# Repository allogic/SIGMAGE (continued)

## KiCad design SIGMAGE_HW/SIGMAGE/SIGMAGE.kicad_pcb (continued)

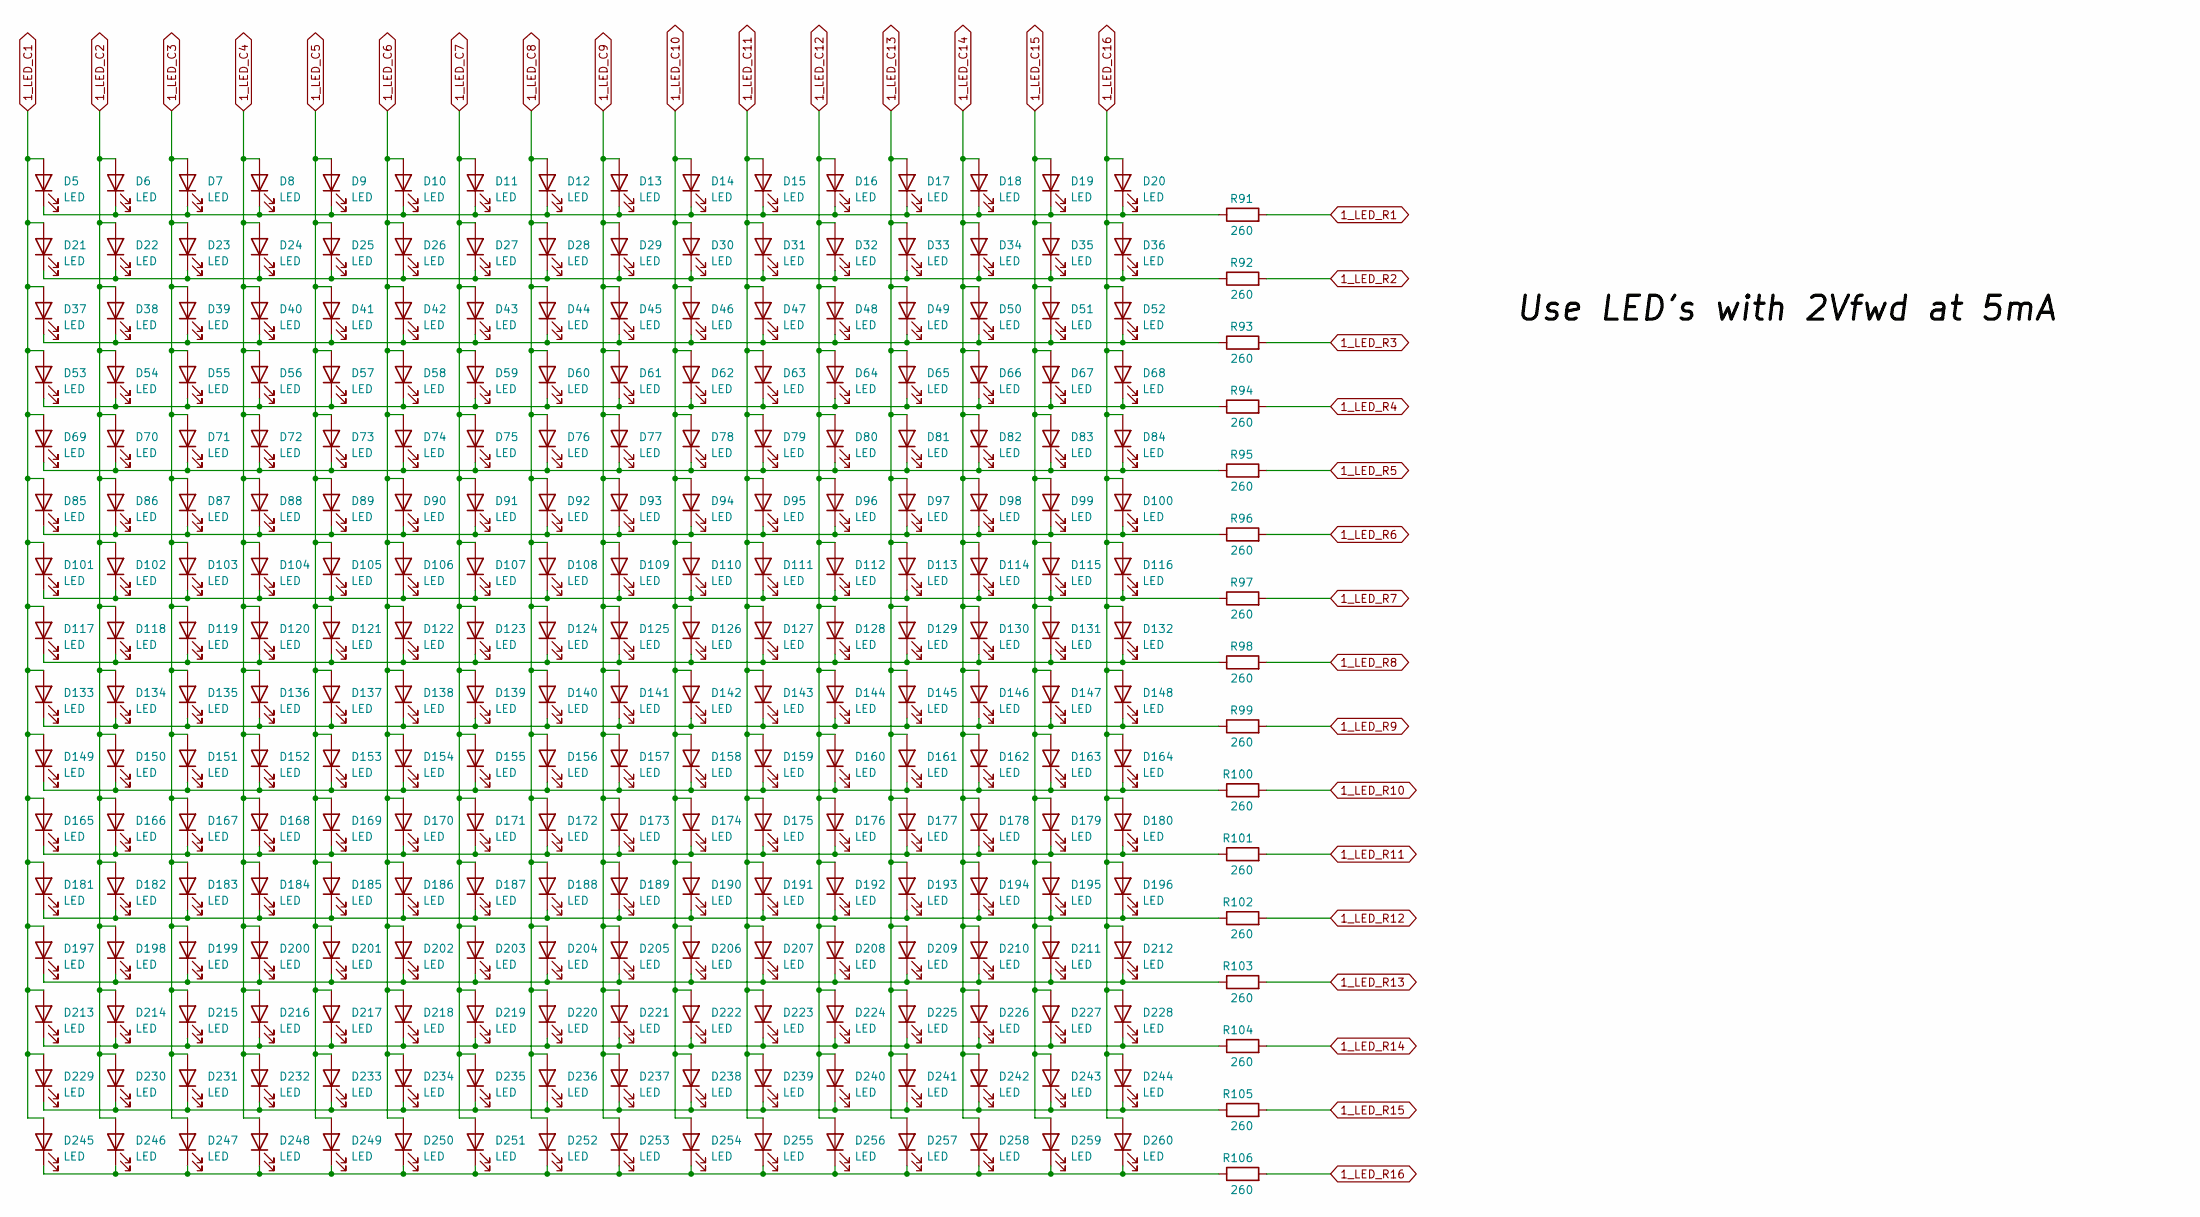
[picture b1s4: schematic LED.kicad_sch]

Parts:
D5, D6, D7, D8, D9, D10, D11, D12, D13, D14, D15, D16, D17, D18, D19, D20, D21, D22, D23, D24, D25, D26, D27, D28, D29, D30, D31, D32, D33, D34, D35, D36, D37, D38, D39, D40, D41, D42, D43, D44, D45, D46, D47, D48, D49, D50, D51, D52, D53, D54, D55, D56, D57, D58, D59, D60, D61, D62, D63, D64, D65, D66, D67, D68, D69, D70, D71, D72, D73, D74, D75, D76, D77, D78, D79, D80, D81, D82, D83, D84, D85, D86, D87, D88, D89, D90, D91, D92, D93, D94, D95, D96, D97, D98, D99, D100, D101, D102, D103, D104, D105, D106, D107, D108, D109, D110, D111, D112, D113, D114, D115, D116, D117, D118, D119, D120, D121, D122, D123, D124, D125, D126, D127, D128, D129, D130, D131, D132, D133, D134, D135, D136, D137, D138, D139, D140, D141, D142, D143, D144, D145, D146, D147, D148, D149, D150, D151, D152, D153, D154, D155, D156, D157, D158, D159, D160, D161, D162, D163, D164, D165, D166, D167, D168, D169, D170, D171, D172, D173, D174, D175, D176, D177, D178, D179, D180, D181, D182, D183, D184, D185, D186, D187, D188, D189, D190, D191, D192, D193, D194, D195, D196, D197, D198, D199, D200, D201, D202, D203, D204, D205, D206, D207, D208, D209, D210, D211, D212, D213, D214, D215, D216, D217, D218, D219, D220, D221, D222, D223, D224, D225, D226, D227, D228, D229, D230, D231, D232, D233, D234, D235, D236, D237, D238, D239, D240, D241, D242, D243, D244, D245, D246, D247, D248, D249, D250, D251, D252, D253, D254, D255, D256, D257, D258, D259, D260: LED; LED_0603_1608Metric
R91, R92, R93, R94, R95, R96, R97, R98, R99, R100, R101, R102, R103, R104, R105, R106: 260; R_0603_1608Metric

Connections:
1_LED_C1: D5.2 (A), D21.2 (A), D37.2 (A), D53.2 (A), D69.2 (A), D85.2 (A), D101.2 (A), D117.2 (A), D133.2 (A), D149.2 (A), D165.2 (A), D181.2 (A), D197.2 (A), D213.2 (A), D229.2 (A), D245.2 (A); also elsewhere on the board
1_LED_C2: D6.2 (A), D22.2 (A), D38.2 (A), D54.2 (A), D70.2 (A), D86.2 (A), D102.2 (A), D118.2 (A), D134.2 (A), D150.2 (A), D166.2 (A), D182.2 (A), D198.2 (A), D214.2 (A), D230.2 (A), D246.2 (A); also elsewhere on the board
1_LED_C3: D7.2 (A), D23.2 (A), D39.2 (A), D55.2 (A), D71.2 (A), D87.2 (A), D103.2 (A), D119.2 (A), D135.2 (A), D151.2 (A), D167.2 (A), D183.2 (A), D199.2 (A), D215.2 (A), D231.2 (A), D247.2 (A); also elsewhere on the board
1_LED_C4: D8.2 (A), D24.2 (A), D40.2 (A), D56.2 (A), D72.2 (A), D88.2 (A), D104.2 (A), D120.2 (A), D136.2 (A), D152.2 (A), D168.2 (A), D184.2 (A), D200.2 (A), D216.2 (A), D232.2 (A), D248.2 (A); also elsewhere on the board
1_LED_C5: D9.2 (A), D25.2 (A), D41.2 (A), D57.2 (A), D73.2 (A), D89.2 (A), D105.2 (A), D121.2 (A), D137.2 (A), D153.2 (A), D169.2 (A), D185.2 (A), D201.2 (A), D217.2 (A), D233.2 (A), D249.2 (A); also elsewhere on the board
1_LED_C6: D10.2 (A), D26.2 (A), D42.2 (A), D58.2 (A), D74.2 (A), D90.2 (A), D106.2 (A), D122.2 (A), D138.2 (A), D154.2 (A), D170.2 (A), D186.2 (A), D202.2 (A), D218.2 (A), D234.2 (A), D250.2 (A); also elsewhere on the board
1_LED_C7: D11.2 (A), D27.2 (A), D43.2 (A), D59.2 (A), D75.2 (A), D91.2 (A), D107.2 (A), D123.2 (A), D139.2 (A), D155.2 (A), D171.2 (A), D187.2 (A), D203.2 (A), D219.2 (A), D235.2 (A), D251.2 (A); also elsewhere on the board
1_LED_C8: D12.2 (A), D28.2 (A), D44.2 (A), D60.2 (A), D76.2 (A), D92.2 (A), D108.2 (A), D124.2 (A), D140.2 (A), D156.2 (A), D172.2 (A), D188.2 (A), D204.2 (A), D220.2 (A), D236.2 (A), D252.2 (A); also elsewhere on the board
1_LED_C9: D13.2 (A), D29.2 (A), D45.2 (A), D61.2 (A), D77.2 (A), D93.2 (A), D109.2 (A), D125.2 (A), D141.2 (A), D157.2 (A), D173.2 (A), D189.2 (A), D205.2 (A), D221.2 (A), D237.2 (A), D253.2 (A); also elsewhere on the board
1_LED_C10: D14.2 (A), D30.2 (A), D46.2 (A), D62.2 (A), D78.2 (A), D94.2 (A), D110.2 (A), D126.2 (A), D142.2 (A), D158.2 (A), D174.2 (A), D190.2 (A), D206.2 (A), D222.2 (A), D238.2 (A), D254.2 (A); also elsewhere on the board
1_LED_C11: D15.2 (A), D31.2 (A), D47.2 (A), D63.2 (A), D79.2 (A), D95.2 (A), D111.2 (A), D127.2 (A), D143.2 (A), D159.2 (A), D175.2 (A), D191.2 (A), D207.2 (A), D223.2 (A), D239.2 (A), D255.2 (A); also elsewhere on the board
1_LED_C12: D16.2 (A), D32.2 (A), D48.2 (A), D64.2 (A), D80.2 (A), D96.2 (A), D112.2 (A), D128.2 (A), D144.2 (A), D160.2 (A), D176.2 (A), D192.2 (A), D208.2 (A), D224.2 (A), D240.2 (A), D256.2 (A); also elsewhere on the board
1_LED_C13: D17.2 (A), D33.2 (A), D49.2 (A), D65.2 (A), D81.2 (A), D97.2 (A), D113.2 (A), D129.2 (A), D145.2 (A), D161.2 (A), D177.2 (A), D193.2 (A), D209.2 (A), D225.2 (A), D241.2 (A), D257.2 (A); also elsewhere on the board
1_LED_C14: D18.2 (A), D34.2 (A), D50.2 (A), D66.2 (A), D82.2 (A), D98.2 (A), D114.2 (A), D130.2 (A), D146.2 (A), D162.2 (A), D178.2 (A), D194.2 (A), D210.2 (A), D226.2 (A), D242.2 (A), D258.2 (A); also elsewhere on the board
1_LED_C15: D19.2 (A), D35.2 (A), D51.2 (A), D67.2 (A), D83.2 (A), D99.2 (A), D115.2 (A), D131.2 (A), D147.2 (A), D163.2 (A), D179.2 (A), D195.2 (A), D211.2 (A), D227.2 (A), D243.2 (A), D259.2 (A); also elsewhere on the board
1_LED_C16: D20.2 (A), D36.2 (A), D52.2 (A), D68.2 (A), D84.2 (A), D100.2 (A), D116.2 (A), D132.2 (A), D148.2 (A), D164.2 (A), D180.2 (A), D196.2 (A), D212.2 (A), D228.2 (A), D244.2 (A), D260.2 (A); also elsewhere on the board
1_LED_R1: R91.2; also elsewhere on the board
1_LED_R2: R92.2; also elsewhere on the board
1_LED_R3: R93.2; also elsewhere on the board
1_LED_R4: R94.2; also elsewhere on the board
1_LED_R5: R95.2; also elsewhere on the board
1_LED_R6: R96.2; also elsewhere on the board
1_LED_R7: R97.2; also elsewhere on the board
1_LED_R8: R98.2; also elsewhere on the board
1_LED_R9: R99.2; also elsewhere on the board
1_LED_R10: R100.2; also elsewhere on the board
1_LED_R11: R101.2; also elsewhere on the board
1_LED_R12: R102.2; also elsewhere on the board
1_LED_R13: R103.2; also elsewhere on the board
1_LED_R14: R104.2; also elsewhere on the board
1_LED_R15: R105.2; also elsewhere on the board
1_LED_R16: R106.2; also elsewhere on the board
unnamed: D5.1 (K), D6.1 (K), D7.1 (K), D8.1 (K), D9.1 (K), D10.1 (K), D11.1 (K), D12.1 (K), D13.1 (K), D14.1 (K), D15.1 (K), D16.1 (K), D17.1 (K), D18.1 (K), D19.1 (K), D20.1 (K), R91.1
unnamed: D21.1 (K), D22.1 (K), D23.1 (K), D24.1 (K), D25.1 (K), D26.1 (K), D27.1 (K), D28.1 (K), D29.1 (K), D30.1 (K), D31.1 (K), D32.1 (K), D33.1 (K), D34.1 (K), D35.1 (K), D36.1 (K), R92.1
unnamed: D37.1 (K), D38.1 (K), D39.1 (K), D40.1 (K), D41.1 (K), D42.1 (K), D43.1 (K), D44.1 (K), D45.1 (K), D46.1 (K), D47.1 (K), D48.1 (K), D49.1 (K), D50.1 (K), D51.1 (K), D52.1 (K), R93.1
unnamed: D53.1 (K), D54.1 (K), D55.1 (K), D56.1 (K), D57.1 (K), D58.1 (K), D59.1 (K), D60.1 (K), D61.1 (K), D62.1 (K), D63.1 (K), D64.1 (K), D65.1 (K), D66.1 (K), D67.1 (K), D68.1 (K), R94.1
unnamed: D69.1 (K), D70.1 (K), D71.1 (K), D72.1 (K), D73.1 (K), D74.1 (K), D75.1 (K), D76.1 (K), D77.1 (K), D78.1 (K), D79.1 (K), D80.1 (K), D81.1 (K), D82.1 (K), D83.1 (K), D84.1 (K), R95.1
unnamed: D85.1 (K), D86.1 (K), D87.1 (K), D88.1 (K), D89.1 (K), D90.1 (K), D91.1 (K), D92.1 (K), D93.1 (K), D94.1 (K), D95.1 (K), D96.1 (K), D97.1 (K), D98.1 (K), D99.1 (K), D100.1 (K), R96.1
unnamed: D101.1 (K), D102.1 (K), D103.1 (K), D104.1 (K), D105.1 (K), D106.1 (K), D107.1 (K), D108.1 (K), D109.1 (K), D110.1 (K), D111.1 (K), D112.1 (K), D113.1 (K), D114.1 (K), D115.1 (K), D116.1 (K), R97.1
unnamed: D117.1 (K), D118.1 (K), D119.1 (K), D120.1 (K), D121.1 (K), D122.1 (K), D123.1 (K), D124.1 (K), D125.1 (K), D126.1 (K), D127.1 (K), D128.1 (K), D129.1 (K), D130.1 (K), D131.1 (K), D132.1 (K), R98.1
unnamed: D133.1 (K), D134.1 (K), D135.1 (K), D136.1 (K), D137.1 (K), D138.1 (K), D139.1 (K), D140.1 (K), D141.1 (K), D142.1 (K), D143.1 (K), D144.1 (K), D145.1 (K), D146.1 (K), D147.1 (K), D148.1 (K), R99.1
unnamed: D149.1 (K), D150.1 (K), D151.1 (K), D152.1 (K), D153.1 (K), D154.1 (K), D155.1 (K), D156.1 (K), D157.1 (K), D158.1 (K), D159.1 (K), D160.1 (K), D161.1 (K), D162.1 (K), D163.1 (K), D164.1 (K), R100.1
unnamed: D165.1 (K), D166.1 (K), D167.1 (K), D168.1 (K), D169.1 (K), D170.1 (K), D171.1 (K), D172.1 (K), D173.1 (K), D174.1 (K), D175.1 (K), D176.1 (K), D177.1 (K), D178.1 (K), D179.1 (K), D180.1 (K), R101.1
unnamed: D181.1 (K), D182.1 (K), D183.1 (K), D184.1 (K), D185.1 (K), D186.1 (K), D187.1 (K), D188.1 (K), D189.1 (K), D190.1 (K), D191.1 (K), D192.1 (K), D193.1 (K), D194.1 (K), D195.1 (K), D196.1 (K), R102.1
unnamed: D197.1 (K), D198.1 (K), D199.1 (K), D200.1 (K), D201.1 (K), D202.1 (K), D203.1 (K), D204.1 (K), D205.1 (K), D206.1 (K), D207.1 (K), D208.1 (K), D209.1 (K), D210.1 (K), D211.1 (K), D212.1 (K), R103.1
unnamed: D213.1 (K), D214.1 (K), D215.1 (K), D216.1 (K), D217.1 (K), D218.1 (K), D219.1 (K), D220.1 (K), D221.1 (K), D222.1 (K), D223.1 (K), D224.1 (K), D225.1 (K), D226.1 (K), D227.1 (K), D228.1 (K), R104.1
unnamed: D229.1 (K), D230.1 (K), D231.1 (K), D232.1 (K), D233.1 (K), D234.1 (K), D235.1 (K), D236.1 (K), D237.1 (K), D238.1 (K), D239.1 (K), D240.1 (K), D241.1 (K), D242.1 (K), D243.1 (K), D244.1 (K), R105.1
unnamed: D245.1 (K), D246.1 (K), D247.1 (K), D248.1 (K), D249.1 (K), D250.1 (K), D251.1 (K), D252.1 (K), D253.1 (K), D254.1 (K), D255.1 (K), D256.1 (K), D257.1 (K), D258.1 (K), D259.1 (K), D260.1 (K), R106.1

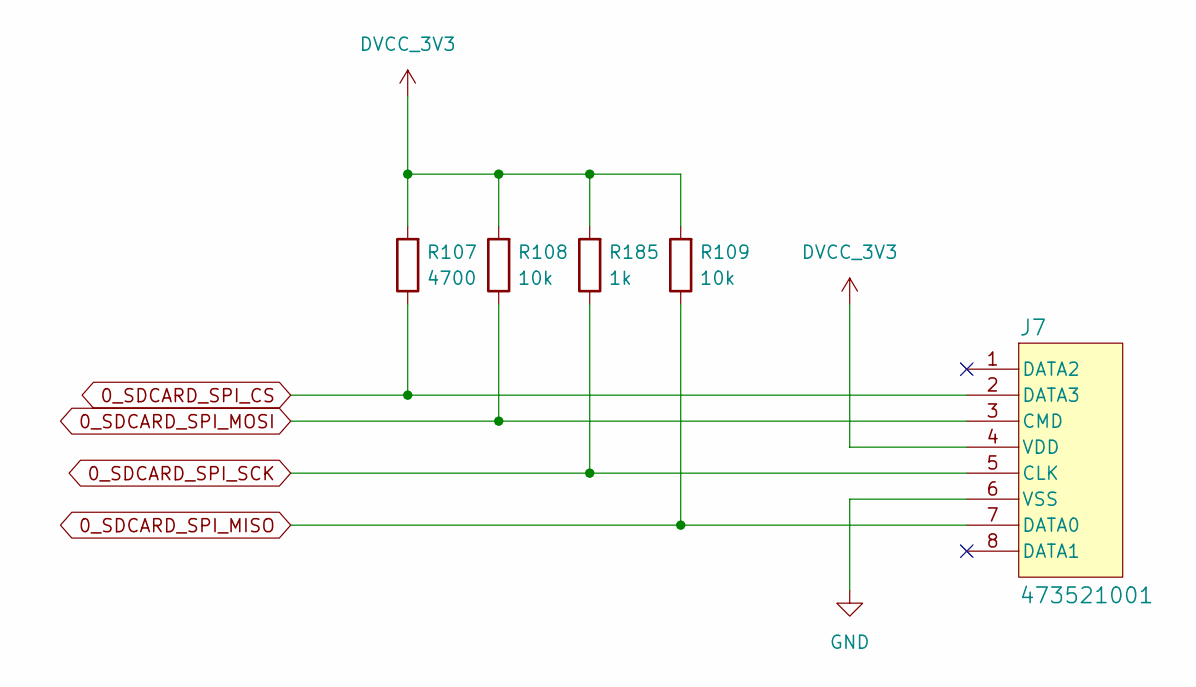
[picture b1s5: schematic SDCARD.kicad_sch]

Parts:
J7: 473521001
R107: 4700; R_0603_1608Metric
R108, R109: 10k; R_0603_1608Metric
R185: 1k; R_0603_1608Metric

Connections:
0_SDCARD_SPI_CS: J7.2 (DATA3), R107.1; also elsewhere on the board
0_SDCARD_SPI_MISO: J7.7 (DATA0), R109.1; also elsewhere on the board
0_SDCARD_SPI_MOSI: J7.3 (CMD), R108.1; also elsewhere on the board
0_SDCARD_SPI_SCK: J7.5 (CLK), R185.1; also elsewhere on the board
DVCC_3V3: J7.4 (VDD), R107.2, R108.2, R109.2, R185.2; also elsewhere on the board
GND: J7.6 (VSS); also elsewhere on the board

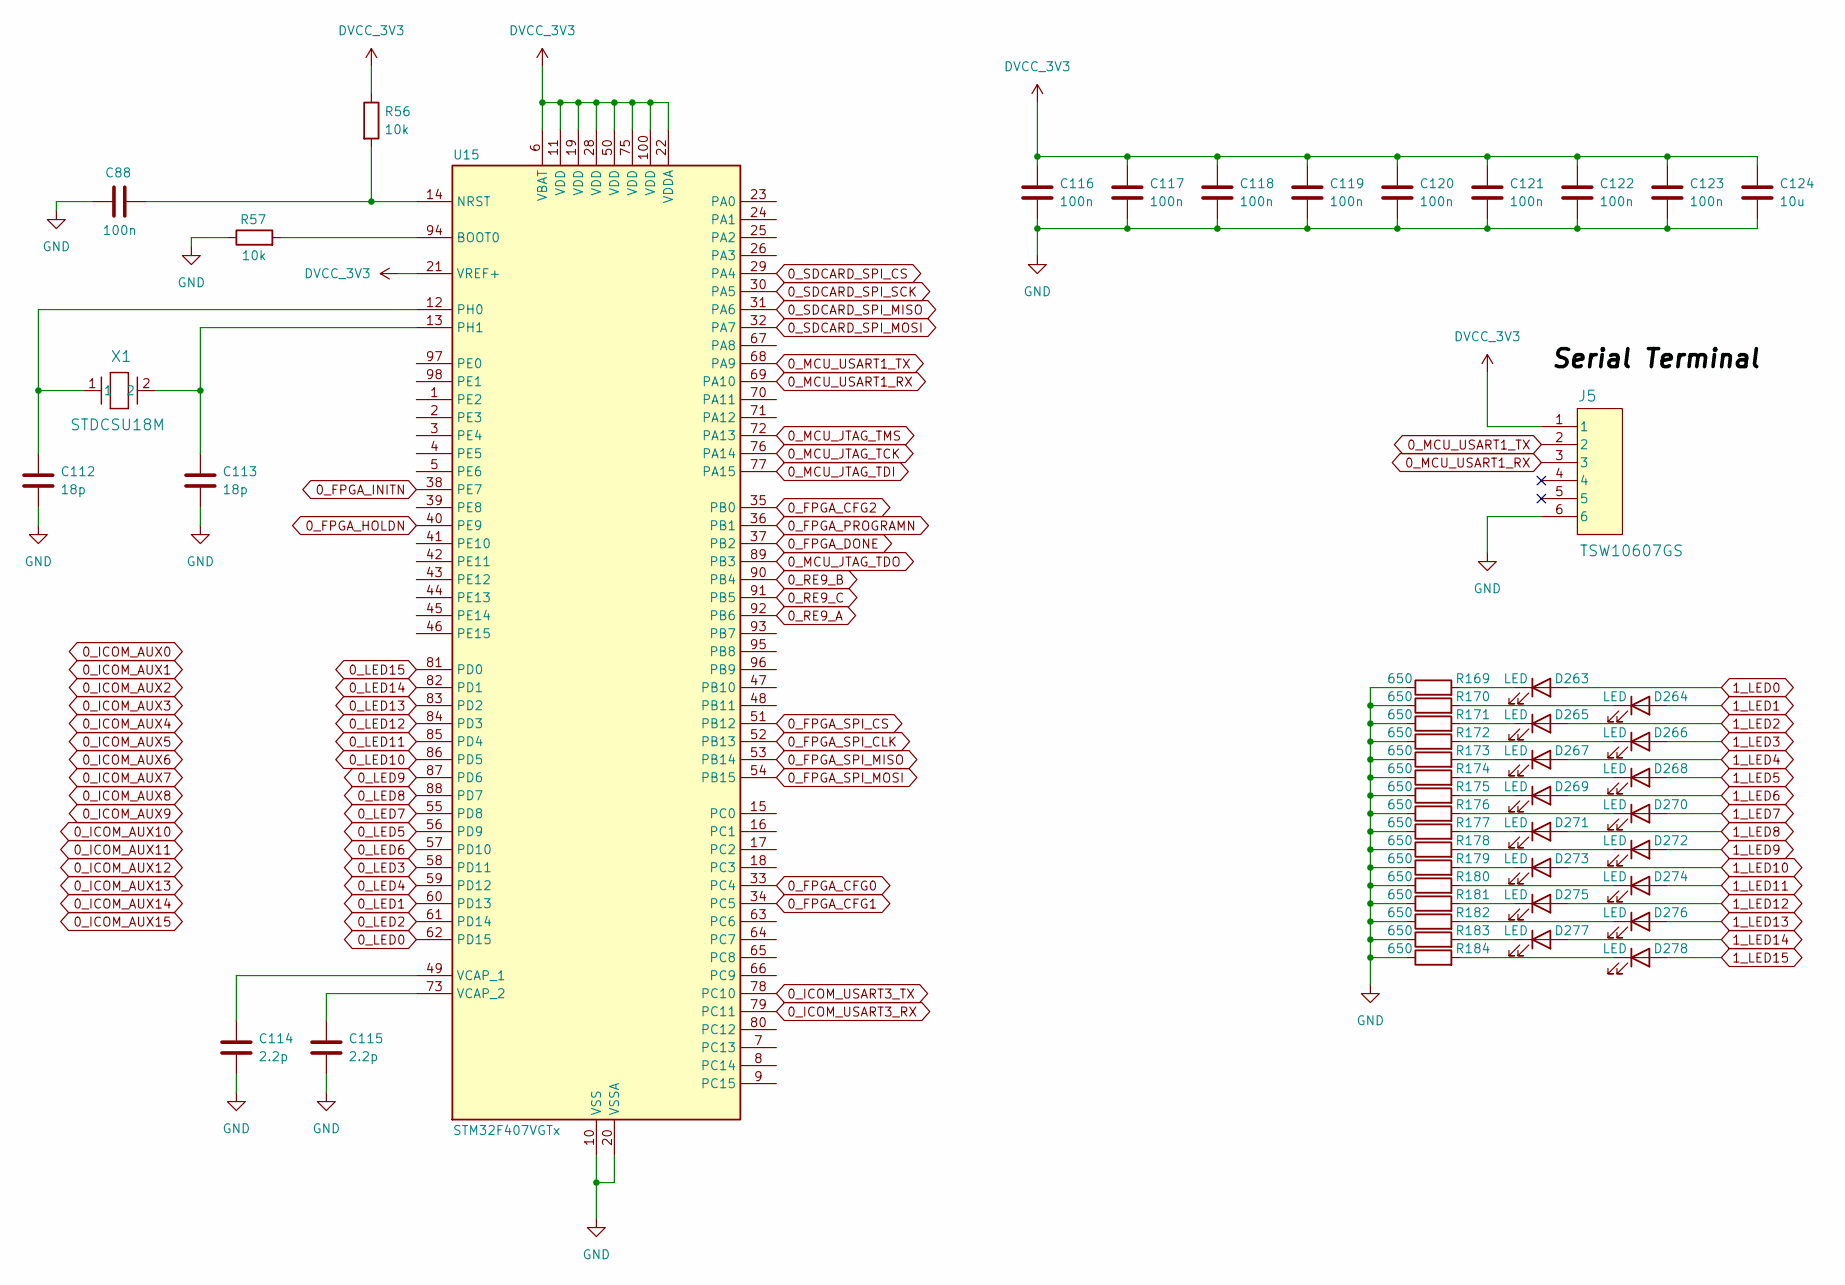
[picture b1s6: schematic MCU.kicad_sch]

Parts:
C88, C116, C117, C118, C119, C120, C121, C122, C123: 100n; C_0603_1608Metric
C112, C113: 18p; C_0603_1608Metric
C114, C115: 2.2p; C_0603_1608Metric
C124: 10u; C_0603_1608Metric
D263, D264, D265, D266, D267, D268, D269, D270, D271, D272, D273, D274, D275, D276, D277, D278: LED; LED_0603_1608Metric
J5: TSW10607GS
R56, R57: 10k; R_0603_1608Metric
R169, R170, R171, R172, R173, R174, R175, R176, R177, R178, R179, R180, R181, R182, R183, R184: 650; R_0603_1608Metric
U15: STM32F407VGTx; LQFP-100_14x14mm_P0.5mm
X1: STDCSU18M

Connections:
0_FPGA_CFG0: U15.33 (PC4); also elsewhere on the board
0_FPGA_CFG1: U15.34 (PC5); also elsewhere on the board
0_FPGA_CFG2: U15.35 (PB0); also elsewhere on the board
0_FPGA_DONE: U15.37 (PB2); also elsewhere on the board
0_FPGA_HOLDN: U15.40 (PE9); also elsewhere on the board
0_FPGA_INITN: U15.38 (PE7); also elsewhere on the board
0_FPGA_PROGRAMN: U15.36 (PB1); also elsewhere on the board
0_FPGA_SPI_CLK: U15.52 (PB13); also elsewhere on the board
0_FPGA_SPI_CS: U15.51 (PB12); also elsewhere on the board
0_FPGA_SPI_MISO: U15.53 (PB14); also elsewhere on the board
0_FPGA_SPI_MOSI: U15.54 (PB15); also elsewhere on the board
0_ICOM_USART3_RX: U15.79 (PC11)
0_ICOM_USART3_TX: U15.78 (PC10)
0_LED0: U15.62 (PD15); also elsewhere on the board
0_LED1: U15.60 (PD13); also elsewhere on the board
0_LED2: U15.61 (PD14); also elsewhere on the board
0_LED3: U15.58 (PD11); also elsewhere on the board
0_LED4: U15.59 (PD12); also elsewhere on the board
0_LED5: U15.56 (PD9); also elsewhere on the board
0_LED6: U15.57 (PD10); also elsewhere on the board
0_LED7: U15.55 (PD8); also elsewhere on the board
0_LED8: U15.88 (PD7); also elsewhere on the board
0_LED9: U15.87 (PD6); also elsewhere on the board
0_LED10: U15.86 (PD5); also elsewhere on the board
0_LED11: U15.85 (PD4); also elsewhere on the board
0_LED12: U15.84 (PD3); also elsewhere on the board
0_LED13: U15.83 (PD2); also elsewhere on the board
0_LED14: U15.82 (PD1); also elsewhere on the board
0_LED15: U15.81 (PD0); also elsewhere on the board
0_MCU_JTAG_TCK: U15.76 (PA14); also elsewhere on the board
0_MCU_JTAG_TDI: U15.77 (PA15); also elsewhere on the board
0_MCU_JTAG_TDO: U15.89 (PB3); also elsewhere on the board
0_MCU_JTAG_TMS: U15.72 (PA13); also elsewhere on the board
0_MCU_USART1_RX: J5.3, U15.69 (PA10)
0_MCU_USART1_TX: J5.2, U15.68 (PA9)
0_RE9_A: U15.92 (PB6); also elsewhere on the board
0_RE9_B: U15.90 (PB4); also elsewhere on the board
0_RE9_C: U15.91 (PB5); also elsewhere on the board
0_SDCARD_SPI_CS: U15.29 (PA4); also elsewhere on the board
0_SDCARD_SPI_MISO: U15.31 (PA6); also elsewhere on the board
0_SDCARD_SPI_MOSI: U15.32 (PA7); also elsewhere on the board
0_SDCARD_SPI_SCK: U15.30 (PA5); also elsewhere on the board
1_LED0: D263.2 (A); also elsewhere on the board
1_LED1: D264.2 (A); also elsewhere on the board
1_LED2: D265.2 (A); also elsewhere on the board
1_LED3: D266.2 (A); also elsewhere on the board
1_LED4: D267.2 (A); also elsewhere on the board
1_LED5: D268.2 (A); also elsewhere on the board
1_LED6: D269.2 (A); also elsewhere on the board
1_LED7: D270.2 (A); also elsewhere on the board
1_LED8: D271.2 (A); also elsewhere on the board
1_LED9: D272.2 (A); also elsewhere on the board
1_LED10: D273.2 (A); also elsewhere on the board
1_LED11: D274.2 (A); also elsewhere on the board
1_LED12: D275.2 (A); also elsewhere on the board
1_LED13: D276.2 (A); also elsewhere on the board
1_LED14: D277.2 (A); also elsewhere on the board
1_LED15: D278.2 (A); also elsewhere on the board
DVCC_3V3: C116.1, C117.1, C118.1, C119.1, C120.1, C121.1, C122.1, C123.1, C124.1, J5.1, R56.1, U15.6 (VBAT), U15.11 (VDD), U15.19 (VDD), U15.21 (VREF+), U15.22 (VDDA), U15.28 (VDD), U15.50 (VDD), U15.75 (VDD), U15.100 (VDD); also elsewhere on the board
GND: C88.1, C112.2, C113.2, C114.2, C115.2, C116.2, C117.2, C118.2, C119.2, C120.2, C121.2, C122.2, C123.2, C124.2, J5.6, R57.1, R169.1, R170.1, R171.1, R172.1, R173.1, R174.1, R175.1, R176.1, R177.1, R178.1, R179.1, R180.1, R181.1, R182.1, R183.1, R184.1, U15.10 (VSS), U15.20 (VSSA), U15.27 (VSS), U15.74 (VSS), U15.99 (VSS); also elsewhere on the board
unnamed: D263.1 (K), R169.2
unnamed: D264.1 (K), R170.2
unnamed: D265.1 (K), R171.2
unnamed: D266.1 (K), R172.2
unnamed: D267.1 (K), R173.2
unnamed: D268.1 (K), R174.2
unnamed: D269.1 (K), R175.2
unnamed: D270.1 (K), R176.2
unnamed: D271.1 (K), R177.2
unnamed: D272.1 (K), R178.2
unnamed: D273.1 (K), R179.2
unnamed: D274.1 (K), R180.2
unnamed: D275.1 (K), R181.2
unnamed: D276.1 (K), R182.2
unnamed: D277.1 (K), R183.2
unnamed: D278.1 (K), R184.2
unnamed: R57.2, U15.94 (BOOT0)
unnamed: C88.2, R56.2, U15.14 (NRST)
unnamed: C112.1, U15.12 (PH0), X1.1
unnamed: C113.1, U15.13 (PH1), X1.2
unnamed: C114.1, U15.49 (VCAP_1)
unnamed: C115.1, U15.73 (VCAP_2)

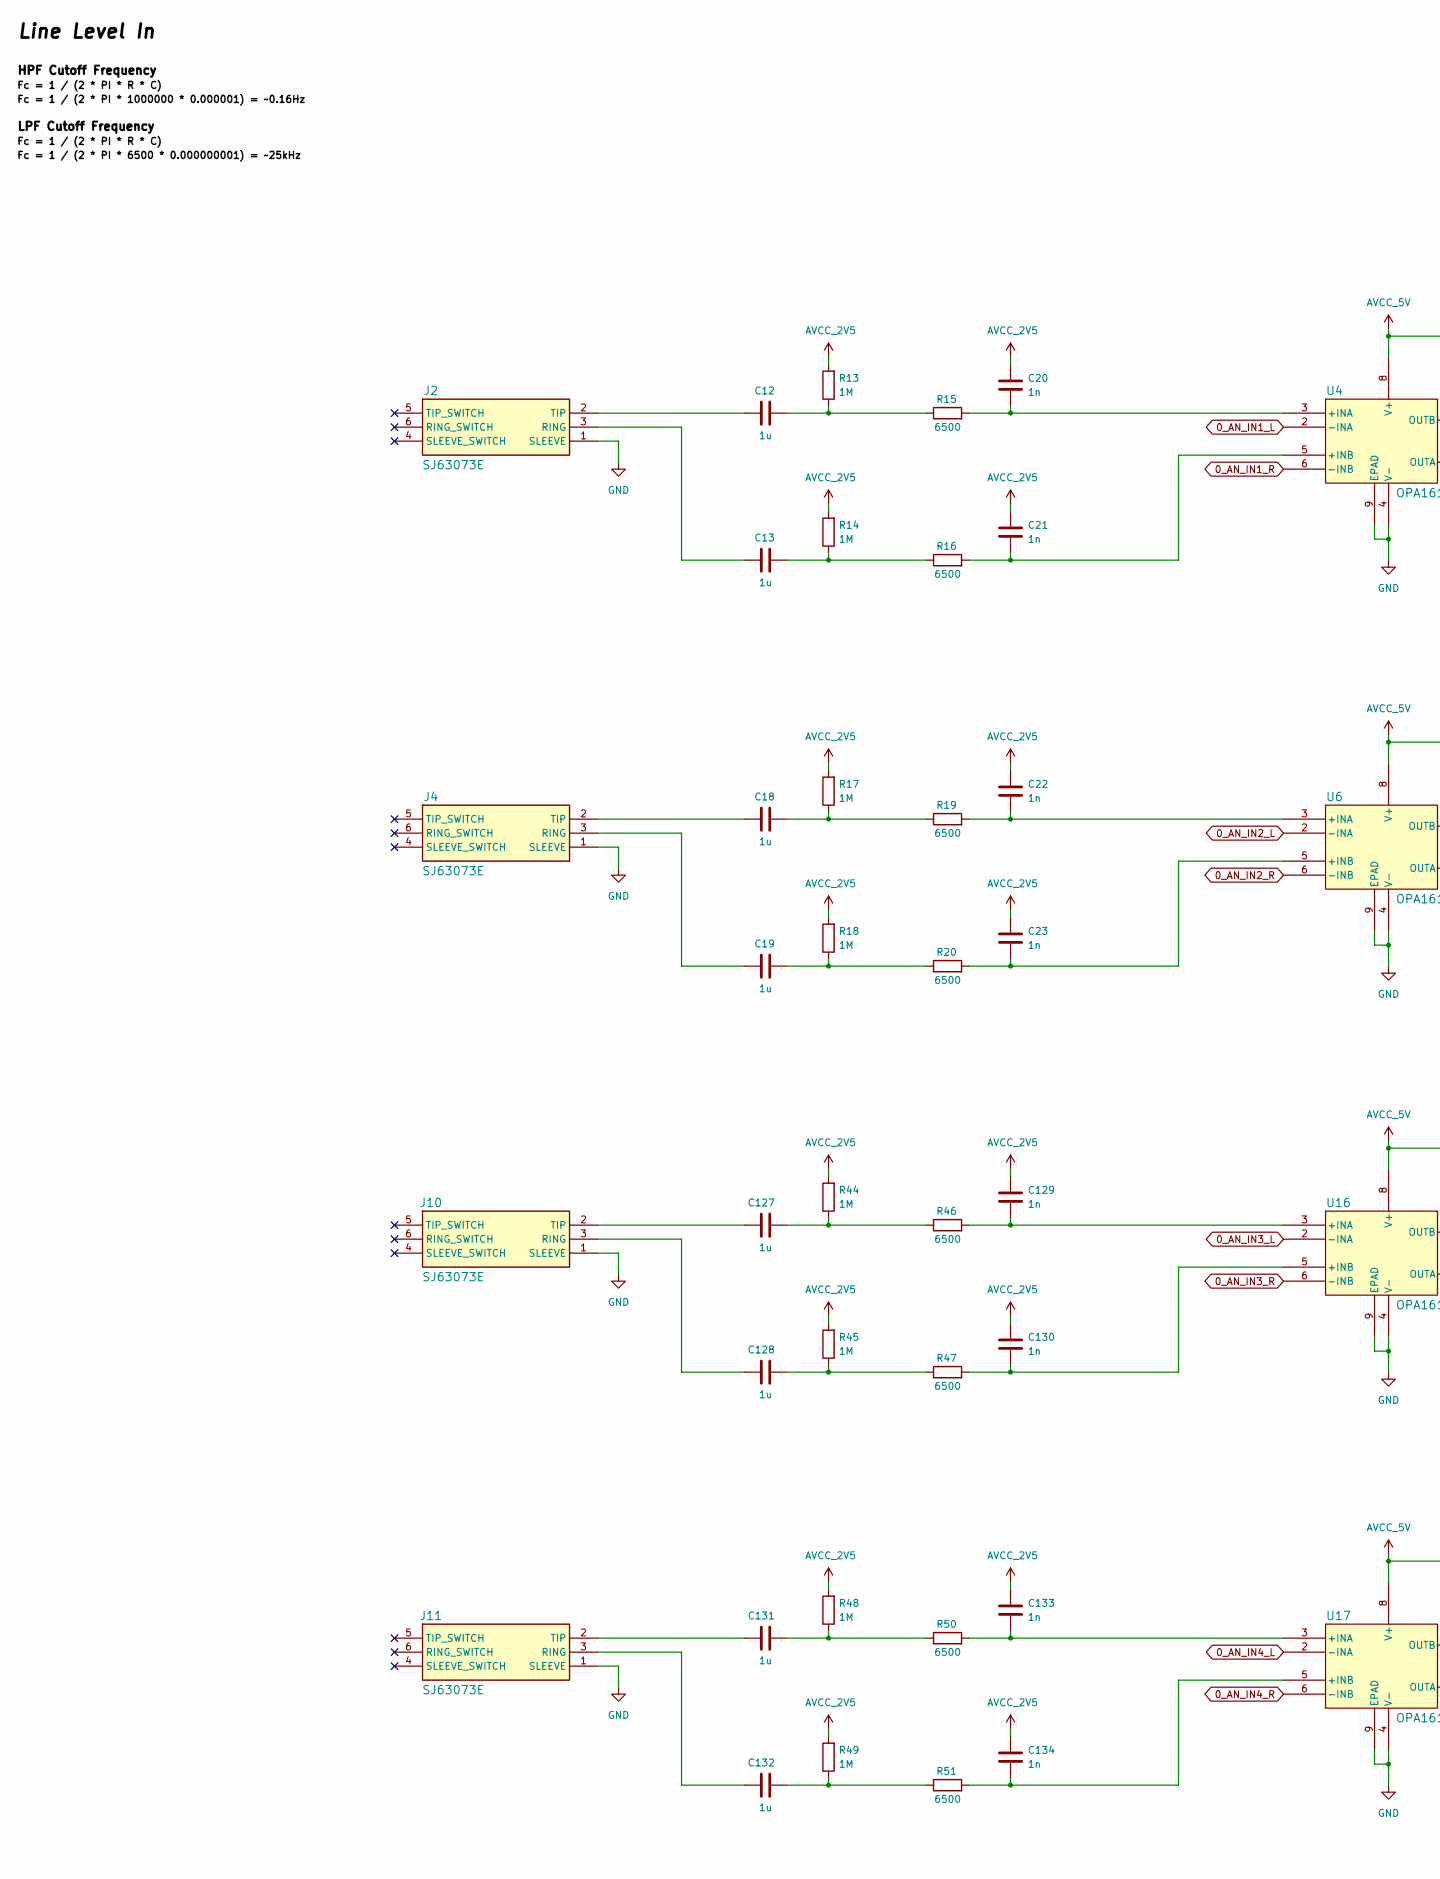
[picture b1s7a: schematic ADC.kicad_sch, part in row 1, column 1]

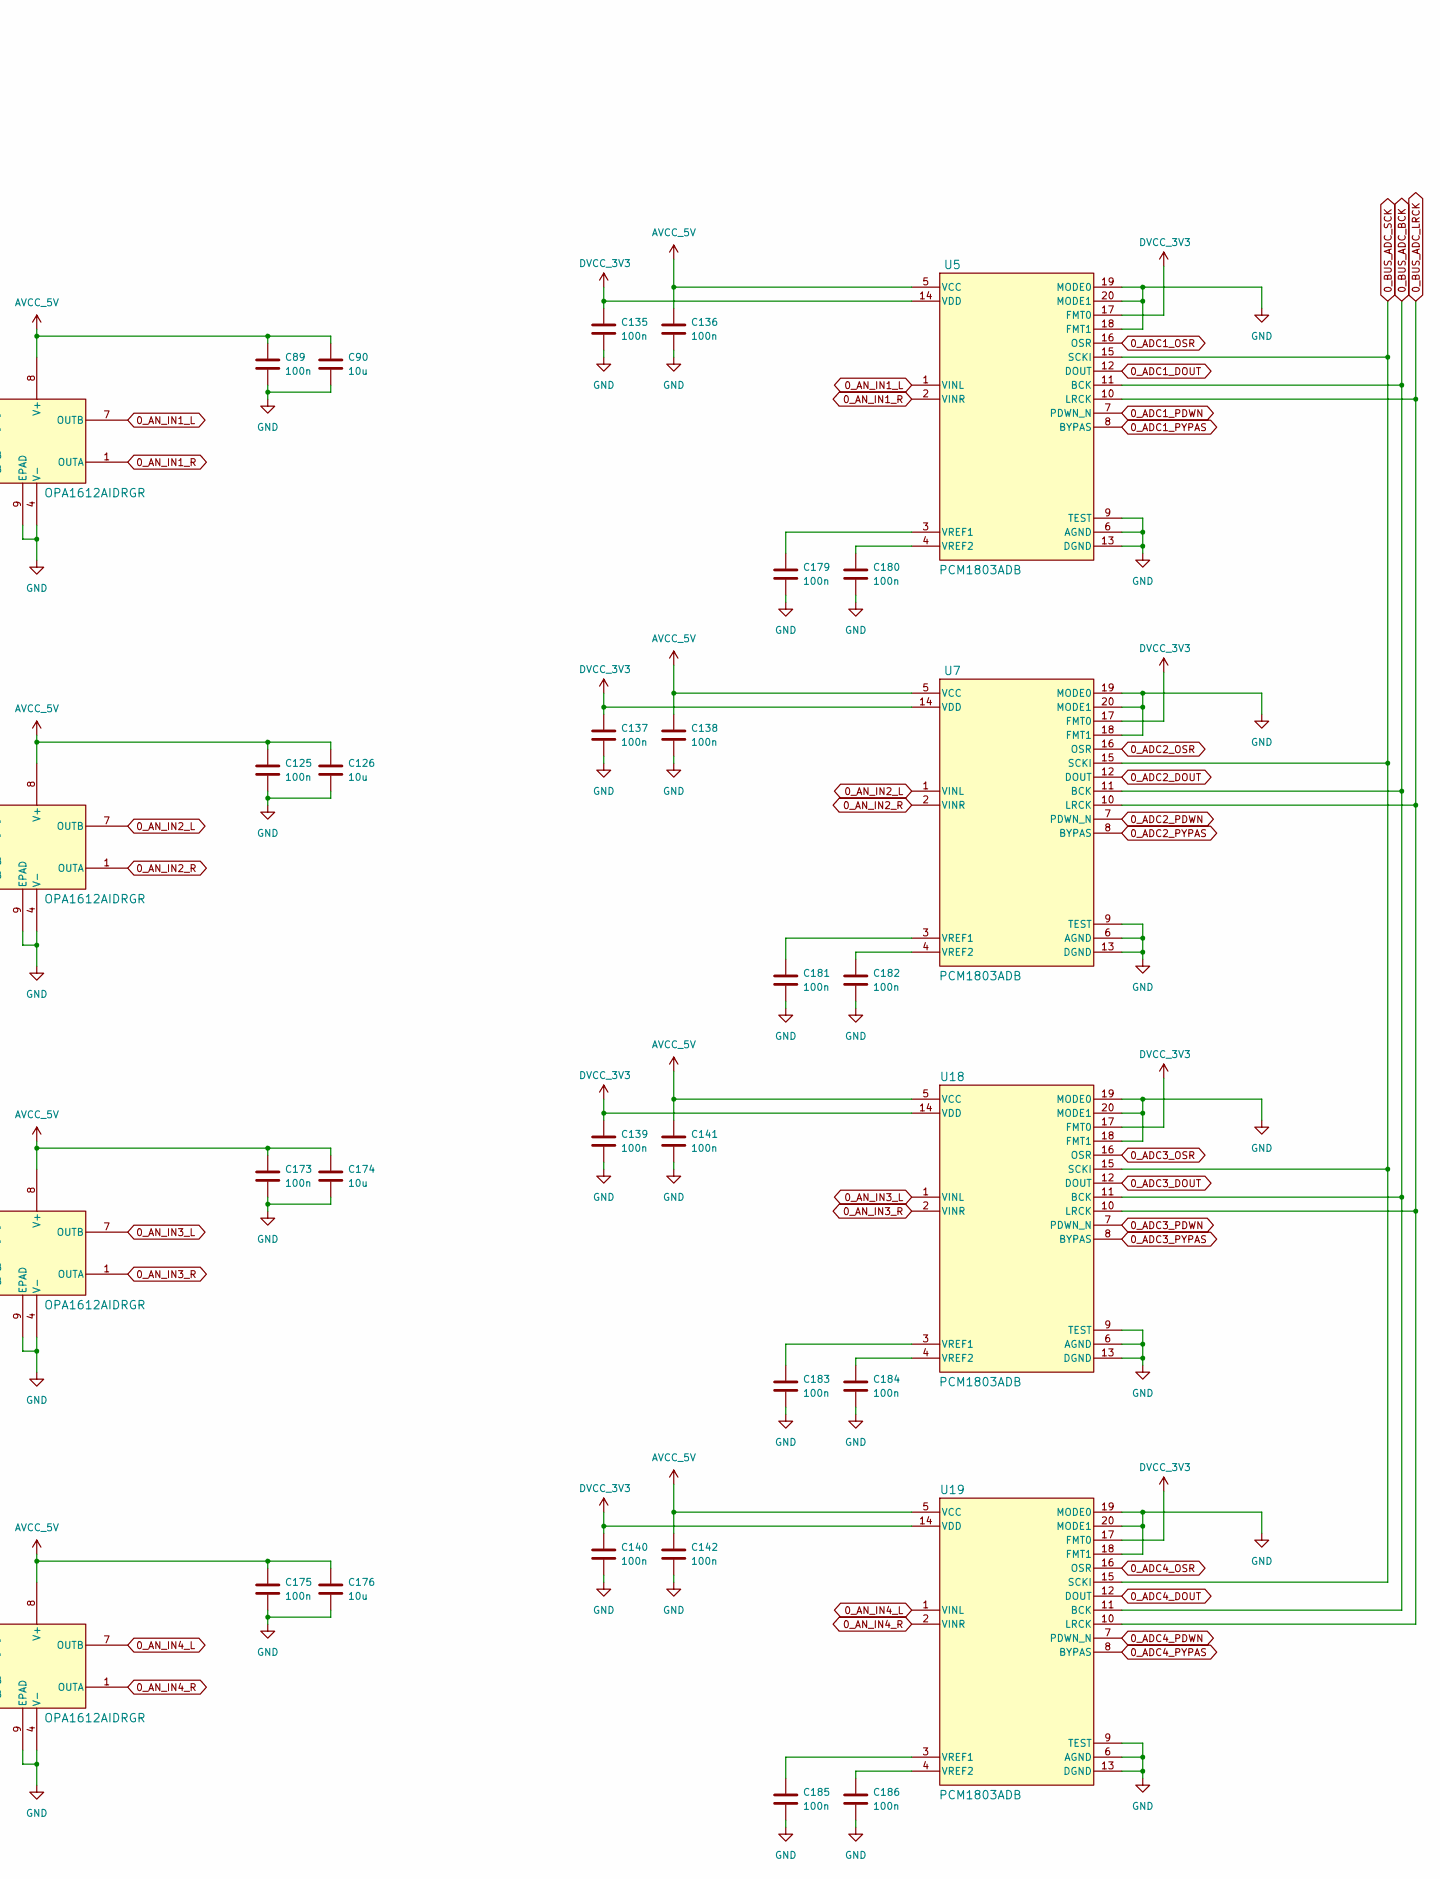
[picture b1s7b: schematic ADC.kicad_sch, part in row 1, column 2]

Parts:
C12, C13, C18, C19, C127, C128, C131, C132: 1u; C_0603_1608Metric
C20, C21, C22, C23, C129, C130, C133, C134: 1n; C_0603_1608Metric
C89, C125, C135, C136, C137, C138, C139, C140, C141, C142, C173, C175, C179, C180, C181, C182, C183, C184, C185, C186: 100n; C_0603_1608Metric
C90, C126, C174, C176: 10u; C_0603_1608Metric
J2, J4, J10, J11: SJ63073E; Manufacturer_Part_Number SJ-63073E; Mouser Part Number 490-SJ-63073E
R13, R14, R17, R18, R44, R45, R48, R49: 1M; R_0603_1608Metric
R15, R16, R19, R20, R46, R47, R50, R51: 6500; R_0603_1608Metric
U4, U6, U16, U17: OPA1612AIDRGR
U5, U7, U18, U19: PCM1803ADB

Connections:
0_ADC1_DOUT: U5.12 (DOUT); also elsewhere on the board
0_ADC1_OSR: U5.16 (OSR); also elsewhere on the board
0_ADC1_PDWN: U5.7 (PDWN_N); also elsewhere on the board
0_ADC1_PYPAS: U5.8 (BYPAS); also elsewhere on the board
0_ADC2_DOUT: U7.12 (DOUT); also elsewhere on the board
0_ADC2_OSR: U7.16 (OSR); also elsewhere on the board
0_ADC2_PDWN: U7.7 (PDWN_N); also elsewhere on the board
0_ADC2_PYPAS: U7.8 (BYPAS); also elsewhere on the board
0_ADC3_DOUT: U18.12 (DOUT); also elsewhere on the board
0_ADC3_OSR: U18.16 (OSR); also elsewhere on the board
0_ADC3_PDWN: U18.7 (PDWN_N); also elsewhere on the board
0_ADC3_PYPAS: U18.8 (BYPAS); also elsewhere on the board
0_ADC4_DOUT: U19.12 (DOUT); also elsewhere on the board
0_ADC4_OSR: U19.16 (OSR); also elsewhere on the board
0_ADC4_PDWN: U19.7 (PDWN_N); also elsewhere on the board
0_ADC4_PYPAS: U19.8 (BYPAS); also elsewhere on the board
0_AN_IN1_L: U4.2 (-INA), U4.7 (OUTB), U5.1 (VINL)
0_AN_IN1_R: U4.1 (OUTA), U4.6 (-INB), U5.2 (VINR)
0_AN_IN2_L: U6.2 (-INA), U6.7 (OUTB), U7.1 (VINL)
0_AN_IN2_R: U6.1 (OUTA), U6.6 (-INB), U7.2 (VINR)
0_AN_IN3_L: U16.2 (-INA), U16.7 (OUTB), U18.1 (VINL)
0_AN_IN3_R: U16.1 (OUTA), U16.6 (-INB), U18.2 (VINR)
0_AN_IN4_L: U17.2 (-INA), U17.7 (OUTB), U19.1 (VINL)
0_AN_IN4_R: U17.1 (OUTA), U17.6 (-INB), U19.2 (VINR)
0_BUS_ADC_BCK: U5.11 (BCK), U7.11 (BCK), U18.11 (BCK), U19.11 (BCK); also elsewhere on the board
0_BUS_ADC_LRCK: U5.10 (LRCK), U7.10 (LRCK), U18.10 (LRCK), U19.10 (LRCK); also elsewhere on the board
0_BUS_ADC_SCK: U5.15 (SCKI), U7.15 (SCKI), U18.15 (SCKI), U19.15 (SCKI); also elsewhere on the board
AVCC_2V5: C20.1, C21.1, C22.1, C23.1, C129.1, C130.1, C133.1, C134.1, R13.2, R14.2, R17.2, R18.2, R44.2, R45.2, R48.2, R49.2; also elsewhere on the board
AVCC_5V: C89.1, C90.1, C125.1, C126.1, C136.1, C138.1, C141.1, C142.1, C173.1, C174.1, C175.1, C176.1, U4.8 (V+), U5.5 (VCC), U6.8 (V+), U7.5 (VCC), U16.8 (V+), U17.8 (V+), U18.5 (VCC), U19.5 (VCC); also elsewhere on the board
DVCC_3V3: C135.1, C137.1, C139.1, C140.1, U5.14 (VDD), U5.17 (FMT0), U7.14 (VDD), U7.17 (FMT0), U18.14 (VDD), U18.17 (FMT0), U19.14 (VDD), U19.17 (FMT0); also elsewhere on the board
GND: C89.2, C90.2, C125.2, C126.2, C135.2, C136.2, C137.2, C138.2, C139.2, C140.2, C141.2, C142.2, C173.2, C174.2, C175.2, C176.2, C179.2, C180.2, C181.2, C182.2, C183.2, C184.2, C185.2, C186.2, J2.1 (SLEEVE), J4.1 (SLEEVE), J10.1 (SLEEVE), J11.1 (SLEEVE), U4.4 (V-), U4.9 (EPAD), U5.6 (AGND), U5.9 (TEST), U5.13 (DGND), U5.18 (FMT1), U5.19 (MODE0), U5.20 (MODE1), U6.4 (V-), U6.9 (EPAD), U7.6 (AGND), U7.9 (TEST), U7.13 (DGND), U7.18 (FMT1), U7.19 (MODE0), U7.20 (MODE1), U16.4 (V-), U16.9 (EPAD), U17.4 (V-), U17.9 (EPAD), U18.6 (AGND), U18.9 (TEST), U18.13 (DGND), U18.18 (FMT1), U18.19 (MODE0), U18.20 (MODE1), U19.6 (AGND), U19.9 (TEST), U19.13 (DGND), U19.18 (FMT1), U19.19 (MODE0), U19.20 (MODE1); also elsewhere on the board
unnamed: C12.2, R13.1, R15.1
unnamed: C13.2, R14.1, R16.1
unnamed: C18.2, R17.1, R19.1
unnamed: C19.2, R18.1, R20.1
unnamed: C127.2, R44.1, R46.1
unnamed: C128.2, R45.1, R47.1
unnamed: C131.2, R48.1, R50.1
unnamed: C132.2, R49.1, R51.1
unnamed: C13.1, J2.3 (RING)
unnamed: C12.1, J2.2 (TIP)
unnamed: C19.1, J4.3 (RING)
unnamed: C18.1, J4.2 (TIP)
unnamed: C128.1, J10.3 (RING)
unnamed: C127.1, J10.2 (TIP)
unnamed: C132.1, J11.3 (RING)
unnamed: C131.1, J11.2 (TIP)
unnamed: C20.2, R15.2, U4.3 (+INA)
unnamed: C21.2, R16.2, U4.5 (+INB)
unnamed: C179.1, U5.3 (VREF1)
unnamed: C180.1, U5.4 (VREF2)
unnamed: C22.2, R19.2, U6.3 (+INA)
unnamed: C23.2, R20.2, U6.5 (+INB)
unnamed: C181.1, U7.3 (VREF1)
unnamed: C182.1, U7.4 (VREF2)
unnamed: C129.2, R46.2, U16.3 (+INA)
unnamed: C130.2, R47.2, U16.5 (+INB)
unnamed: C133.2, R50.2, U17.3 (+INA)
unnamed: C134.2, R51.2, U17.5 (+INB)
unnamed: C183.1, U18.3 (VREF1)
unnamed: C184.1, U18.4 (VREF2)
unnamed: C185.1, U19.3 (VREF1)
unnamed: C186.1, U19.4 (VREF2)
